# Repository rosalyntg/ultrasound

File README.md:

# Ultrasound

This repository contains the PCB design files, FPGA firmware files, and host software for a hobby 8 channel ultrasound system. It can do phased array operation. Here's an example of the pulse in my forearm:

Picture of the functioning ultrasound system:

## Overview

The parts of the ultrasound consist of:
- The probe, which is a Acuvision 4V1c probe bought off ebay
    - As far as I can tell, it has 112 elements. I think a bunch of them are broken for this unit, so I've atttempted to work around as best as possible
- The power board
    - This provides a variable voltage positive and negative rails for the pulser, -80V to +80V, as well as various low voltage supplies for the rest of the system (2.5V, 3.3V, +10V, -10V)
- The main logic board
    - Contains an AXAU15 FPGA SOM
      - 10G ethernet
      - JESD204b for the ADCs
      - Pulser logic
      - VGA control logic
      - Power supply control logic
    - 2x Ti ADC34J22 quad ADCs
        - And clock synthesis IC (Si5338)
    - 4x AD8332 dual LNA/VGA
    - 2x HV7321 quad ultrasound pulsers
    - Variable rate linear ramp circuit to control VGA gain
    - 10G ethernet interface
- Probe breakout board
    - Breaks out the connections from the probe to the main logic board, allowing for use of different probes without reworking the main board every time

The FPGA streams all the ADC data (~4Gbps) out the ethernet port to be processed on a host computer. The software programms beamforming patterns into the FPGA and interprets the ADC data

## Repo Tour

- `fpga/` - Contains the FPGA firmware that runs on the AXAU15 FPGA SOM
- `host/` - Contains the host software that communicates with the FPGA and processes the ADC data
- `pcb/ultrasound` - Contains the PCB design files for the main board
- `pcb/probe` - Contains the PCB design files for the probe breakout board
- `pcb/power-board` - Contains the PCB design files for the power board
- `pcb/simulations` - Contains various supporting spice simulations

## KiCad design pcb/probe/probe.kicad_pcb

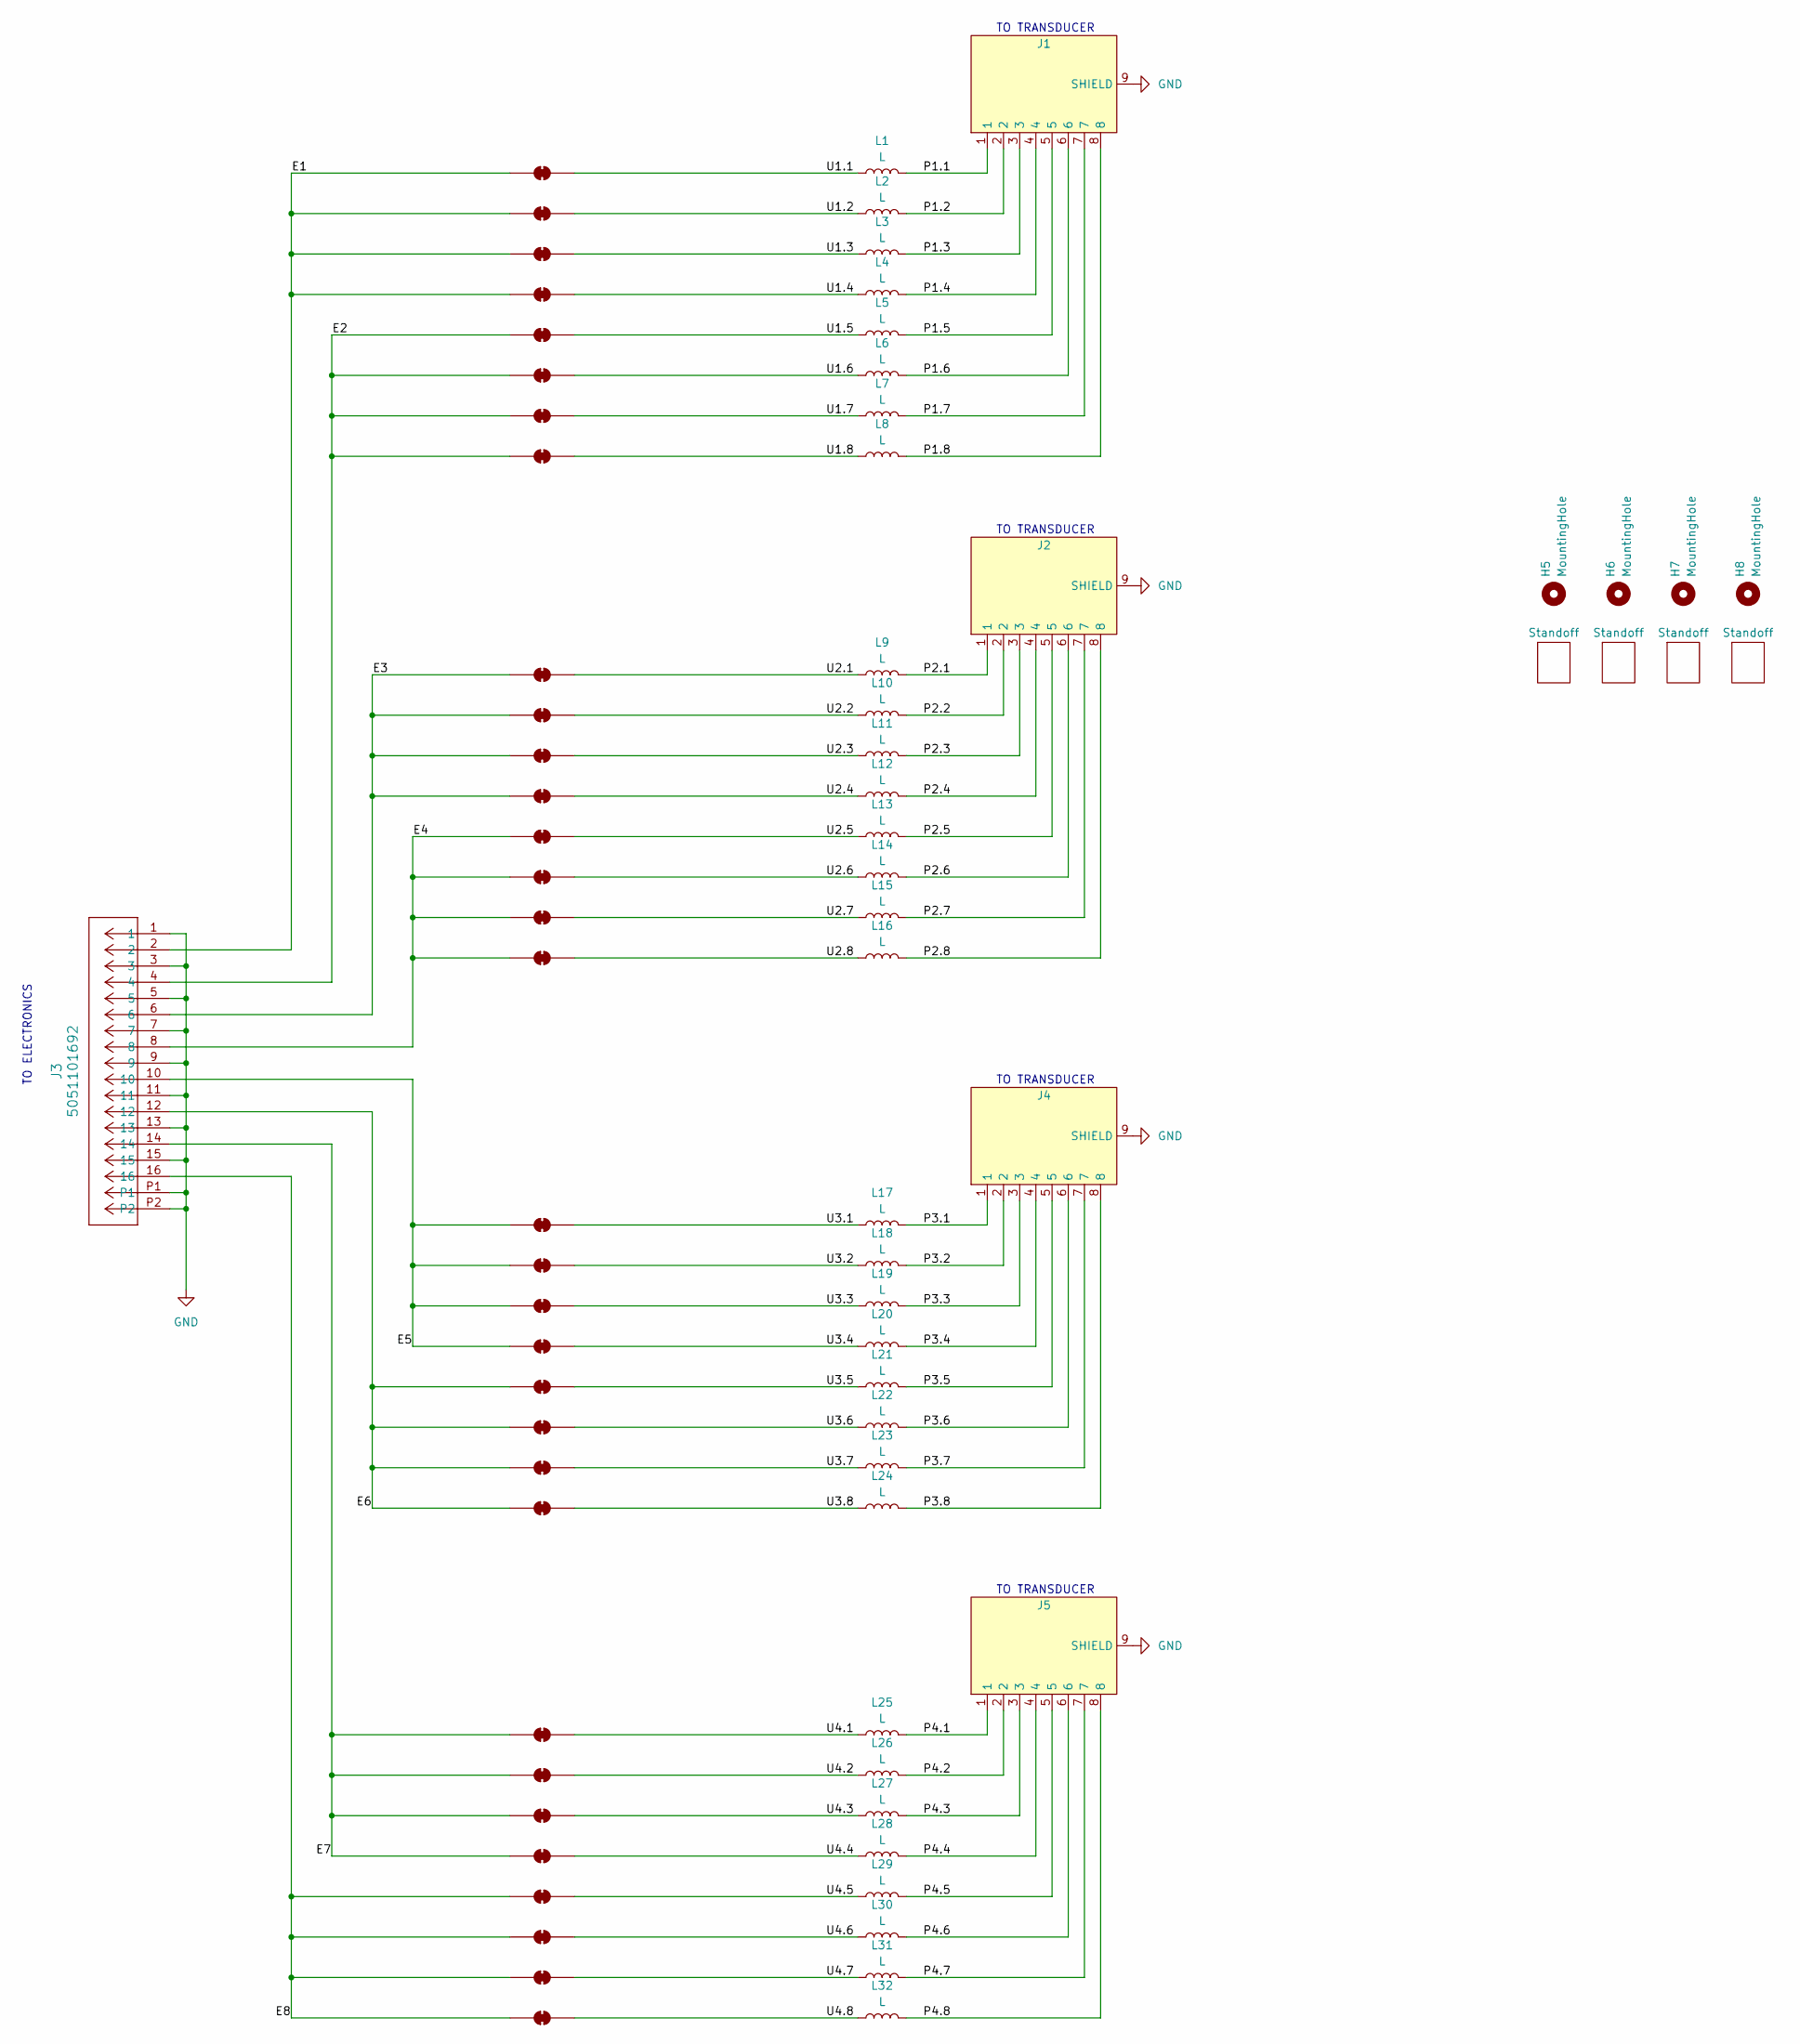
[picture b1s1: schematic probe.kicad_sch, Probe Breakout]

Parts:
H5, H6, H7, H8: MountingHole; MountingHole_3.2mm_M3
J1, J2, J4, J5: UCOAX
J3: 5051101692; CON_5051101692_MOL; Manufacturer Part Number 5051101692; Digikey Part Number WM12372CT-ND
JP2, JP3, JP4, JP5, JP6, JP7, JP8, JP9, JP10, JP11, JP12, JP13, JP14, JP15, JP16, JP17, JP18, JP19, JP20, JP21, JP22, JP23, JP24, JP25, JP26, JP27, JP28, JP29, JP30, JP31, JP32, JP33: SolderJumper_2_Bridged; SolderJumper-2_P1.3mm_Bridged_RoundedPad1.0x1.5mm
L1, L2, L3, L4, L5, L6, L7, L8, L9, L10, L11, L12, L13, L14, L15, L16, L17, L18, L19, L20, L21, L22, L23, L24, L25, L26, L27, L28, L29, L30, L31, L32: L; PROBE_INDUCTOR
Z8, Z9, Z10, Z11: Standoff; Manufacturer_Part_Number 24438; DigiKey Part Number 36-24438-ND

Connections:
/E1: J3.2, JP2.1 (A), JP3.1 (A), JP4.1 (A), JP5.1 (A)
/E2: J3.4, JP6.1 (A), JP7.1 (A), JP8.1 (A), JP9.1 (A)
/E3: J3.6, JP10.1 (A), JP11.1 (A), JP12.1 (A), JP13.1 (A)
/E4: J3.8, JP14.1 (A), JP15.1 (A), JP16.1 (A), JP17.1 (A)
/E5: J3.10, JP18.1 (A), JP19.1 (A), JP20.1 (A), JP21.1 (A)
/E6: J3.12, JP22.1 (A), JP23.1 (A), JP24.1 (A), JP25.1 (A)
/E7: J3.14, JP26.1 (A), JP27.1 (A), JP28.1 (A), JP29.1 (A)
/E8: J3.16, JP30.1 (A), JP31.1 (A), JP32.1 (A), JP33.1 (A)
/P1.1: J1.1, L1.2
/P1.2: J1.2, L2.2
/P1.3: J1.3, L3.2
/P1.4: J1.4, L4.2
/P1.5: J1.5, L5.2
/P1.6: J1.6, L6.2
/P1.7: J1.7, L7.2
/P1.8: J1.8, L8.2
/P2.1: J2.1, L9.2
/P2.2: J2.2, L10.2
/P2.3: J2.3, L11.2
/P2.4: J2.4, L12.2
/P2.5: J2.5, L13.2
/P2.6: J2.6, L14.2
/P2.7: J2.7, L15.2
/P2.8: J2.8, L16.2
/P3.1: J4.1, L17.2
/P3.2: J4.2, L18.2
/P3.3: J4.3, L19.2
/P3.4: J4.4, L20.2
/P3.5: J4.5, L21.2
/P3.6: J4.6, L22.2
/P3.7: J4.7, L23.2
/P3.8: J4.8, L24.2
/P4.1: J5.1, L25.2
/P4.2: J5.2, L26.2
/P4.3: J5.3, L27.2
/P4.4: J5.4, L28.2
/P4.5: J5.5, L29.2
/P4.6: J5.6, L30.2
/P4.7: J5.7, L31.2
/P4.8: J5.8, L32.2
/U1.1: JP2.2 (B), L1.1
/U1.2: JP3.2 (B), L2.1
/U1.3: JP4.2 (B), L3.1
/U1.4: JP5.2 (B), L4.1
/U1.5: JP6.2 (B), L5.1
/U1.6: JP7.2 (B), L6.1
/U1.7: JP8.2 (B), L7.1
/U1.8: JP9.2 (B), L8.1
/U2.1: JP10.2 (B), L9.1
/U2.2: JP11.2 (B), L10.1
/U2.3: JP12.2 (B), L11.1
/U2.4: JP13.2 (B), L12.1
/U2.5: JP14.2 (B), L13.1
/U2.6: JP15.2 (B), L14.1
/U2.7: JP16.2 (B), L15.1
/U2.8: JP17.2 (B), L16.1
/U3.1: JP18.2 (B), L17.1
/U3.2: JP19.2 (B), L18.1
/U3.3: JP20.2 (B), L19.1
/U3.4: JP21.2 (B), L20.1
/U3.5: JP22.2 (B), L21.1
/U3.6: JP23.2 (B), L22.1
/U3.7: JP24.2 (B), L23.1
/U3.8: JP25.2 (B), L24.1
/U4.1: JP26.2 (B), L25.1
/U4.2: JP27.2 (B), L26.1
/U4.3: JP28.2 (B), L27.1
/U4.4: JP29.2 (B), L28.1
/U4.5: JP30.2 (B), L29.1
/U4.6: JP31.2 (B), L30.1
/U4.7: JP32.2 (B), L31.1
/U4.8: JP33.2 (B), L32.1
GND: J1.9 (SHIELD), J2.9 (SHIELD), J3.1, J3.3, J3.5, J3.7, J3.9, J3.11, J3.13, J3.15, J3.P1, J3.P2, J4.9 (SHIELD), J5.9 (SHIELD)

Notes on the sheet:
TO ELECTRONICS
TO TRANSDUCER

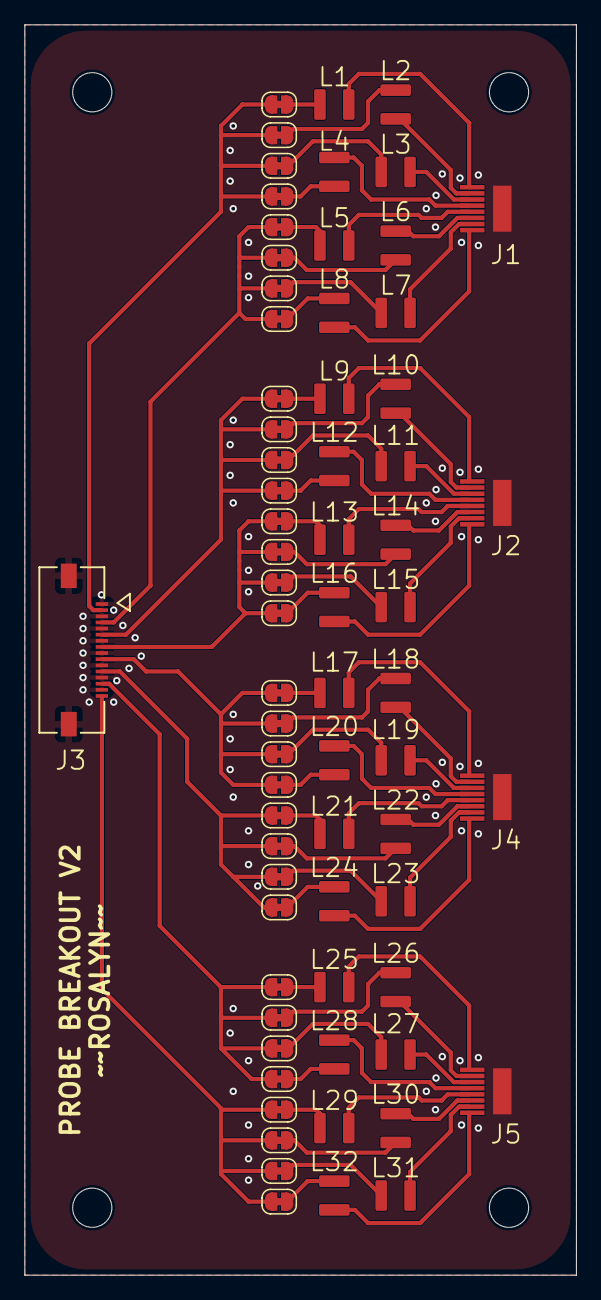
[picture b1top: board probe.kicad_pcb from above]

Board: 2 copper layers, 45.0 x 102.0 mm, 73 parts (0 on the bottom side), 73 nets.

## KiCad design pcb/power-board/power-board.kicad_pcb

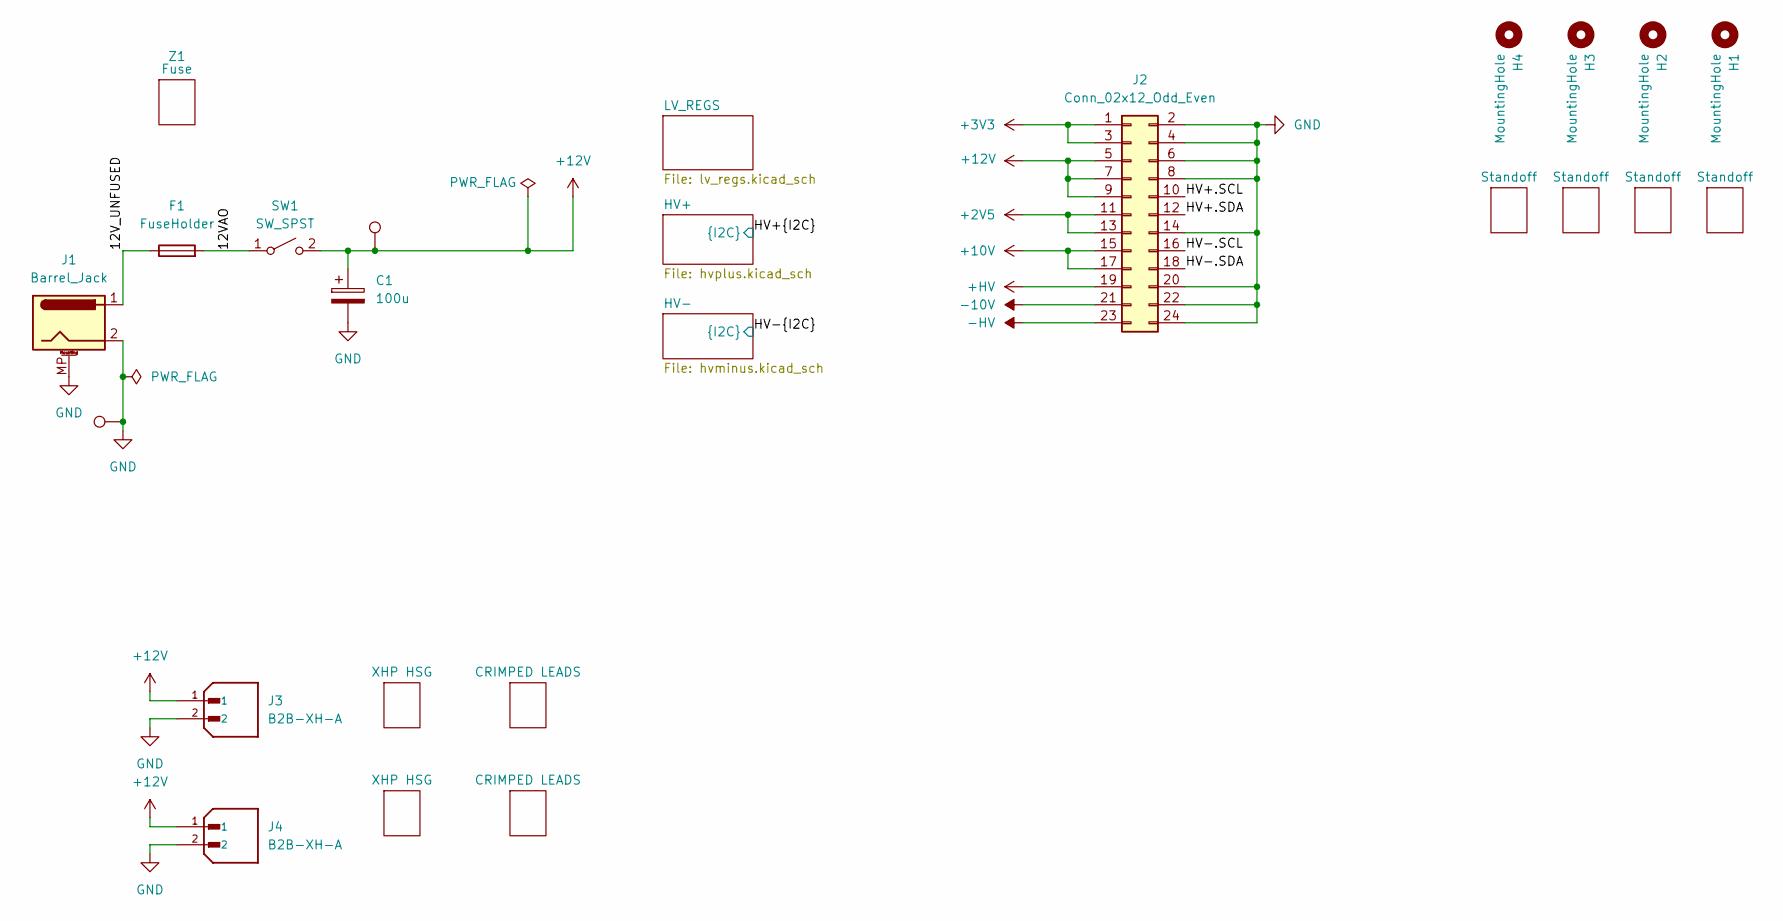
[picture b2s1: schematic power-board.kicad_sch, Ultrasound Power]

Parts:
C1: 100u; CP_Radial_D5.0mm_P2.00mm; Voltage Rating 16V; Manufacturer_Part_Number 860010372006; DigiKey Part Number 732-8598-3-ND
F1: FuseHolder; Fuseholder_Blade_Mini_Keystone_3568; Manufacturer_Part_Number 3568; DigiKey Part Number 36-3568-ND
H1, H2, H3, H4: MountingHole; MountingHole_3.2mm_M3
J1: Barrel_Jack; BarrelJack_CUI_PJ-063AH_Horizontal; Manufacturer_Part_Number PJ-063AH; DigiKey Part Number CP-063AH-ND
J2: Conn_02x12_Odd_Even; PinSocket_2x12_P2.54mm_Horizontal; Manufacturer_Part_Number PPPC122LJBN-RC; DigiKey Part Number S5565-ND
J3, J4: B2B-XH-A; JST_XH_B2B-XH-AM_1x02_P2.50mm_Vertical; Manufacturer_Part_Number B2B-XH-A; DigiKey Part Number 455-B2B-XH-A-ND
SW1: SW_SPST; CK_L101011; Manufacturer_Part_Number L101011MS02Q; DigiKey Part Number CKC5106-ND
TP1, TP2: TestPoint; TestPoint_THTPad_2.5x2.5mm_Drill1.2mm
Z1: Fuse; Manufacturer_Part_Number 0297005.WXNV; DigiKey Part Number F989-ND
Z8, Z9, Z10, Z11: Standoff; Manufacturer_Part_Number 24438; DigiKey Part Number 36-24438-ND
Z12, Z13: XHP HSG; Manufacturer_Part_Number XHP-2; DigiKey Part Number 455-2266-ND
Z14, Z15: CRIMPED LEADS; Manufacturer_Part_Number ASXHSXH22K305; DigiKey Part Number 455-3241-ND

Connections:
+2V5: J2.11, J2.13; also elsewhere on the board
+3V3: J2.1, J2.3; also elsewhere on the board
+10V: J2.15, J2.17; also elsewhere on the board
+12V: C1.1, J2.5, J2.7, J2.9, J3.1, J4.1, SW1.2 (B), TP2.1 (1_1); also elsewhere on the board
+HV: J2.19; also elsewhere on the board
-10V: J2.21; also elsewhere on the board
-HV: J2.23; also elsewhere on the board
/12VAO: F1.2, SW1.1 (A)
/12V_UNFUSED: F1.1, J1.1
/HV+.SCL: J2.10; also elsewhere on the board
/HV+.SDA: J2.12; also elsewhere on the board
/HV-.SCL: J2.16; also elsewhere on the board
/HV-.SDA: J2.18; also elsewhere on the board
GND: C1.2, J1.2, J1.MP (MountPin_MP), J2.2, J2.4, J2.6, J2.8, J2.14, J2.20, J2.22, J2.24, J3.2, J4.2, TP1.1 (1_1); also elsewhere on the board

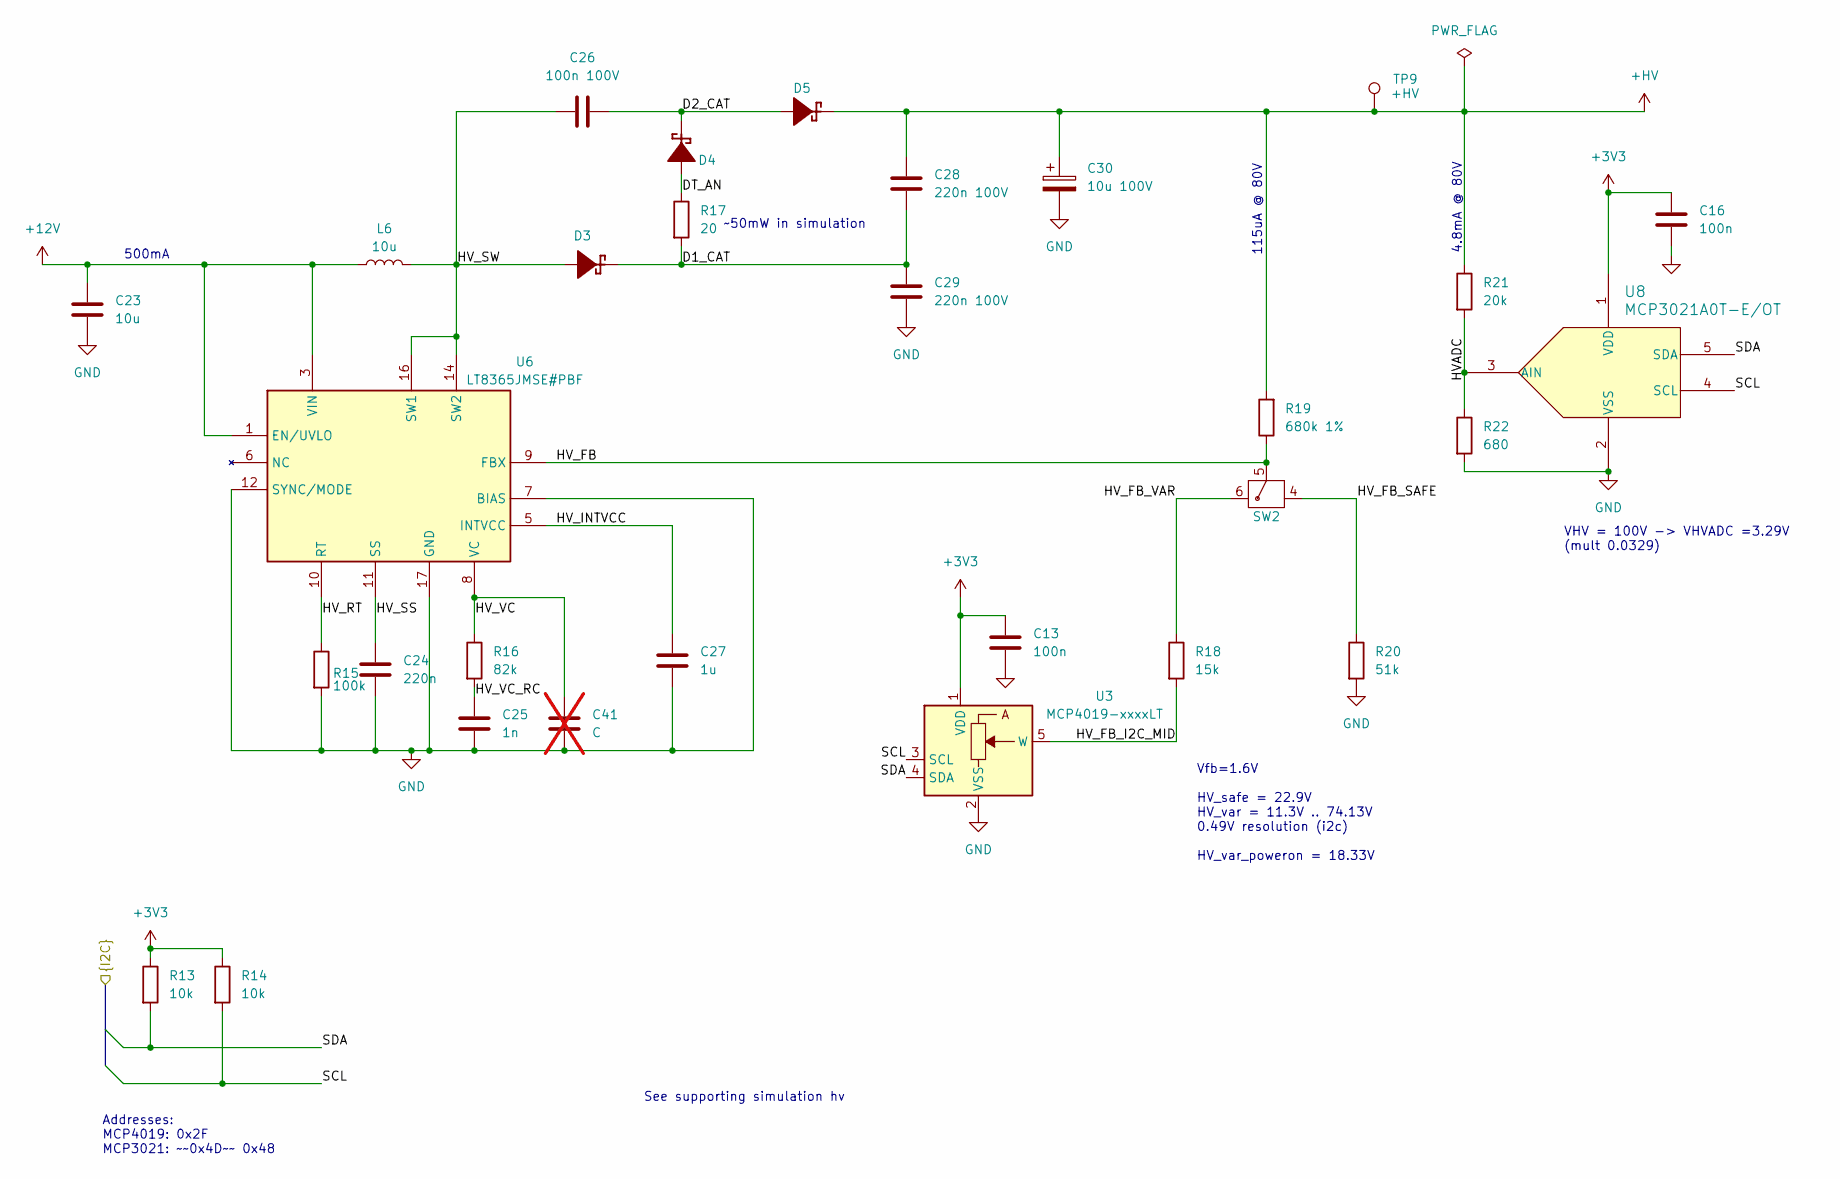
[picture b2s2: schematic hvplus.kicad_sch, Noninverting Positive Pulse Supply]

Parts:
C13, C16: 100n; C_0805_2012Metric_Pad1.18x1.45mm_HandSolder; Voltage Rating 25V; Manufacturer_Part_Number GCM21BR71E104KA37L; DigiKey Part Number 490-14779-1-ND
C23: 10u; C_0805_2012Metric_Pad1.18x1.45mm_HandSolder; Voltage Rating 25V; Manufacturer_Part_Number GRM21BR61E106KA73K; DigiKey Part Number 490-16824-2-ND
C24: 220n; C_0805_2012Metric_Pad1.18x1.45mm_HandSolder; Voltage Rating 25V; Manufacturer_Part_Number GRM219R71E224KA01D; DigiKey Part Number 490-1675-2-ND
C25: 1n; C_0805_2012Metric_Pad1.18x1.45mm_HandSolder; Voltage Rating 50V; Manufacturer_Part_Number GRM216R71H102KA01D
C26: 100n 100V; C_0805_2012Metric_Pad1.18x1.45mm_HandSolder; Voltage Rating 100V; Manufacturer_Part_Number GCM21BR72A104KA37L; DigiKey Part Number 490-4789-1-ND
C27: 1u; C_0805_2012Metric_Pad1.18x1.45mm_HandSolder; Voltage Rating 10V; Manufacturer_Part_Number GRM21BR71A105KA01L
C28, C29: 220n 100V; C_1210_3225Metric_Pad1.33x2.70mm_HandSolder; Voltage Rating 200V; Manufacturer_Part_Number GRM32DR72D224KW01L; DigiKey Part Number 490-13380-1-ND
C30: 10u 100V; CP_Radial_D10.0mm_P5.00mm; Voltage Rating 200V; Manufacturer_Part_Number ECA-2DHG100; DigiKey Part Number P19449-ND
C41: C; C_0805_2012Metric_Pad1.18x1.45mm_HandSolder; not fitted
D3, D4, D5: SMD1150PL-TP; SMD1150PL; Voltage Rating 150V; Mouser Part Number 621-DFLS1150-7
L6: 10u; WURTH_WE-LHMI-4.45mm; Mouser Part Number 710-74437324100
R13, R14: 10k; R_0805_2012Metric_Pad1.20x1.40mm_HandSolder; Manufacturer_Part_Number RC0805JR-0710K
R15: 100k; R_0805_2012Metric_Pad1.20x1.40mm_HandSolder; Manufacturer_Part_Number RC0805JR-07100R; DigiKey Part Number 311-107KCRCT-ND
R16: 82k; R_0805_2012Metric_Pad1.20x1.40mm_HandSolder; Manufacturer_Part_Number RC0805JR-0782K
R17: 20; R_0805_2012Metric_Pad1.20x1.40mm_HandSolder; Manufacturer_Part_Number RC0805JR-0720R
R18: 15k; R_0805_2012Metric_Pad1.20x1.40mm_HandSolder; Manufacturer_Part_Number RC0805FR-0712KL; DigiKey Part Number RC0805JR-0715K
R19: 680k 1%; R_0805_2012Metric_Pad1.20x1.40mm_HandSolder; Manufacturer_Part_Number RC0805FR-07680KL; DigiKey Part Number 311-680KCRCT-ND
R20: 51k; R_0805_2012Metric_Pad1.20x1.40mm_HandSolder; Manufacturer_Part_Number RC0805JR0751K; DigiKey Part Number 311-51KARCT-ND
R21: 20k; R_0805_2012Metric_Pad1.20x1.40mm_HandSolder; Manufacturer_Part_Number RC0805FR-071ML; DigiKey Part Number 311-1.00MCRCT-ND
R22: 680; R_0805_2012Metric_Pad1.20x1.40mm_HandSolder; Manufacturer_Part_Number AC0805FR-0727KL; DigiKey Part Number 13-AC0805FR-0727KLCT-ND
SW2: CST11T2CR; Manufacturer_Part_Number CST11T2CR; DigiKey Part Number 2449-CST11T2CR-ND
TP9: TestPoint; TestPoint_THTPad_2.5x2.5mm_Drill1.2mm
U3: MCP4019-xxxxLT; SOT-353_SC-70-5; Manufacturer_Part_Number MCP4018T-104E/LTY; DigiKey Part Number 150-MCP4018T-104E/LTYCT-ND
U6: LT8365JMSE#PBF; LT8365JMSEPBF; Mouser Part Number 584-LT8365JMSE#PBF
U8: MCP3021A0T-E/OT; SOT-23-5_MC_MCH-M; Manufacturer_Part_Number MCP3021A0T-E/OT; DigiKey Part Number MCP3021A0T-E/OTCT-ND

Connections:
+3V3: C13.1, C16.1, R13.1, R14.1, U3.1 (VDD), U8.1 (VDD); also elsewhere on the board
+12V: C23.1, L6.1, U6.1 (EN/UVLO), U6.3 (VIN); also elsewhere on the board
+HV: C28.1, C30.1, D5.1 (K), R19.2, R21.1, TP9.1 (1_1); also elsewhere on the board
/HV+.SCL: R14.2, U3.3 (SCL), U8.4 (SCL); also elsewhere on the board
/HV+.SDA: R13.2, U3.4 (SDA), U8.5 (SDA); also elsewhere on the board
/HV+/D1_CAT: C28.2, C29.1, D3.1 (K), R17.2
/HV+/D2_CAT: C26.2, D4.1 (K), D5.2 (A)
/HV+/DT_AN: D4.2 (A), R17.1
/HV+/HVADC: R21.2, R22.1, U8.3 (AIN)
/HV+/HV_FB: R19.1, SW2.5, U6.9 (FBX)
/HV+/HV_FB_I2C_MID: R18.2, U3.5 (W)
/HV+/HV_FB_SAFE: R20.1, SW2.4
/HV+/HV_FB_VAR: R18.1, SW2.6
/HV+/HV_INTVCC: C27.1, U6.5 (INTVCC)
/HV+/HV_RT: R15.1, U6.10 (RT)
/HV+/HV_SS: C24.1, U6.11 (SS)
/HV+/HV_SW: C26.1, D3.2 (A), L6.2, U6.14 (SW2), U6.16 (SW1)
/HV+/HV_VC: C41.1, R16.1, U6.8 (VC)
/HV+/HV_VC_RC: C25.1, R16.2
GND: C13.2, C16.2, C23.2, C24.2, C25.2, C27.2, C29.2, C30.2, C41.2, R15.2, R20.2, R22.2, U3.2 (VSS), U6.7 (BIAS), U6.12 (SYNC/MODE), U6.17 (GND), U8.2 (VSS); also elsewhere on the board

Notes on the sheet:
4.8mA @ 80V
~50mW in simulation
500mA
See supporting simulation hv
115uA @ 80V
Vfb=1.6V HV_safe = 22.9V HV_var = 11.3V .. 74.13V 0.49V resolution (i2c) HV_var_poweron = 18.33V
VHV = 100V -> VHVADC =3.29V (mult 0.0329)
Addresses: MCP4019: 0x2F MCP3021: ~~0x4D~~ 0x48

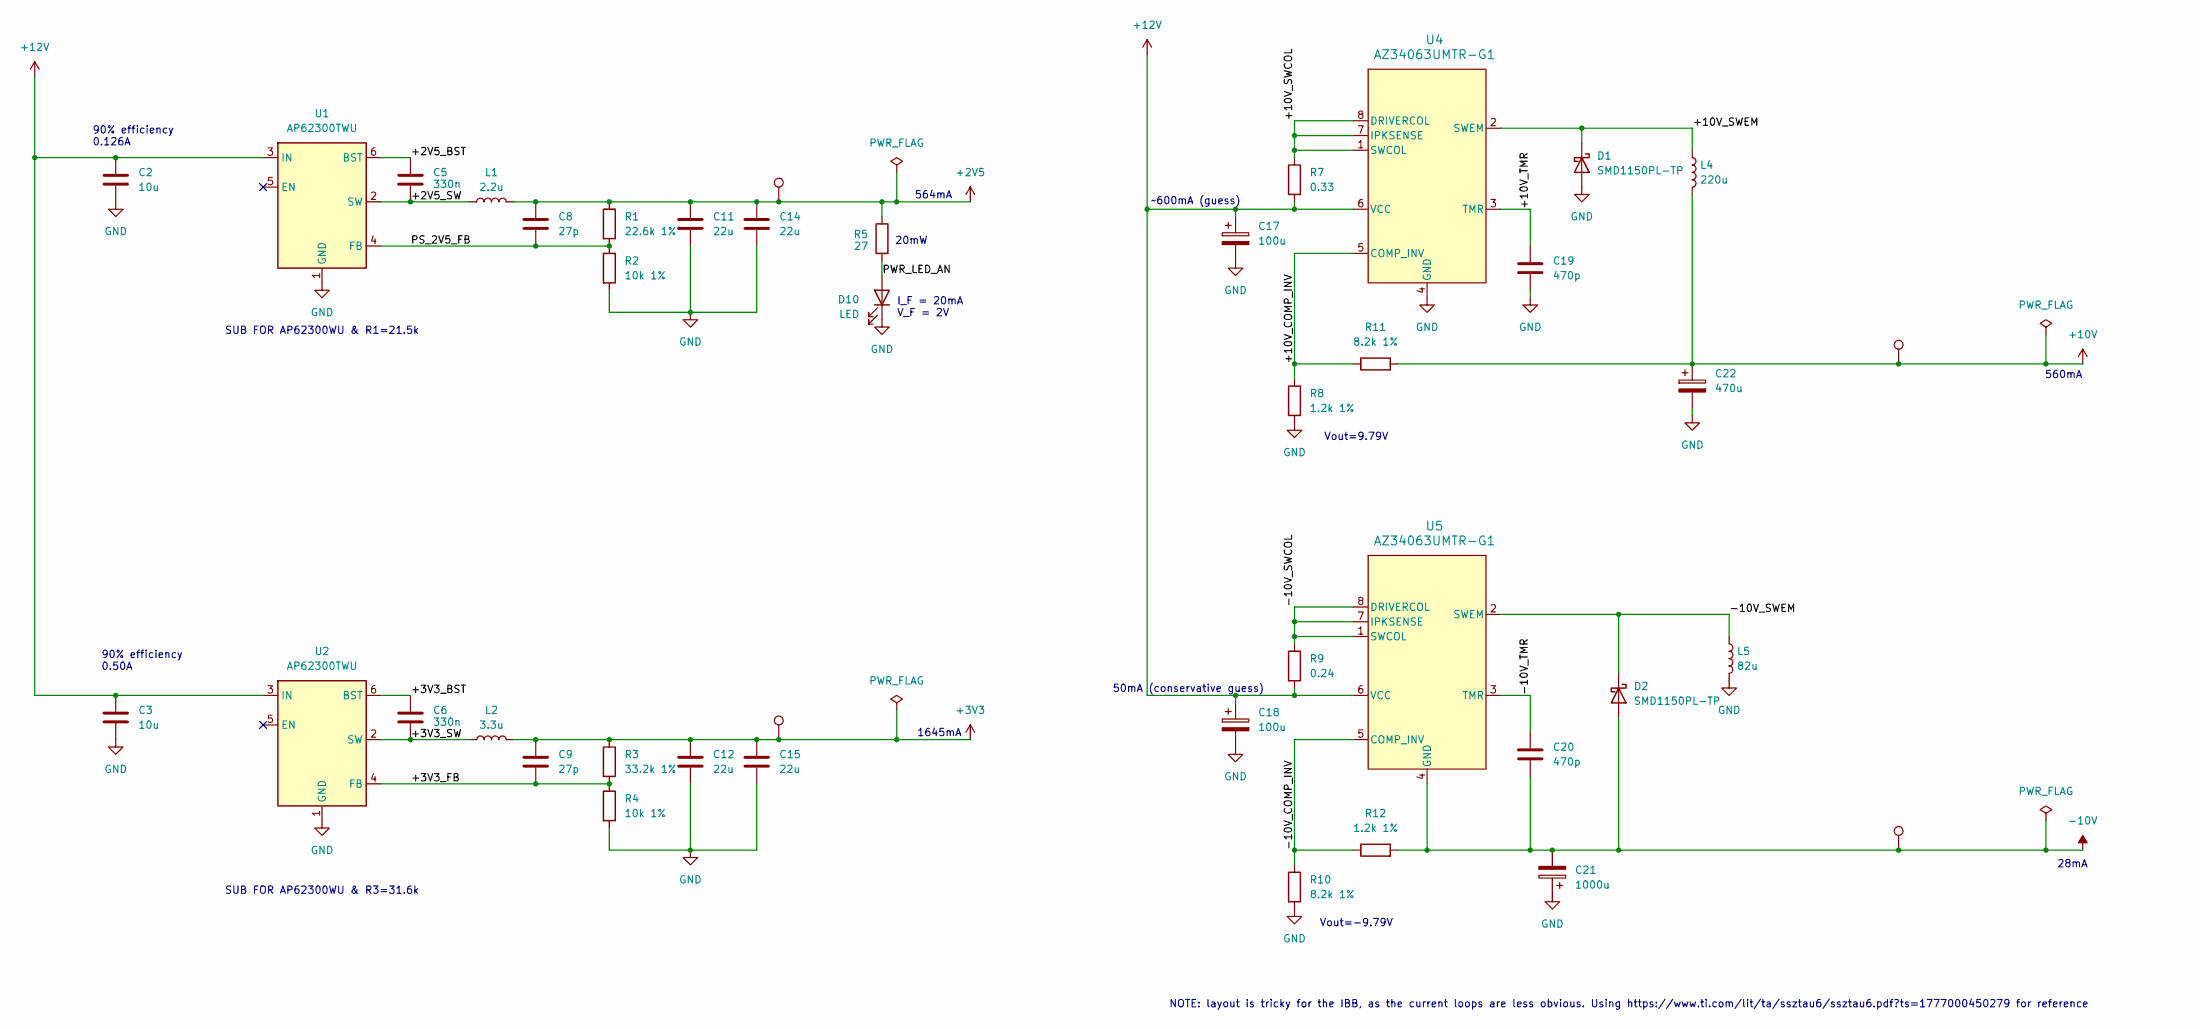
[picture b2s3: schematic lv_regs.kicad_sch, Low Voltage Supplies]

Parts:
C2, C3: 10u; C_0805_2012Metric_Pad1.18x1.45mm_HandSolder; Voltage Rating 25V; Manufacturer_Part_Number GRM21BR61E106KA73K; DigiKey Part Number 490-16824-2-ND
C5, C6: 330n; C_0805_2012Metric_Pad1.18x1.45mm_HandSolder; Voltage Rating 25V; Manufacturer_Part_Number GRM31C5C1E334JE01L; DigiKey Part Number 490-1677-2-ND
C8, C9: 27p; C_0805_2012Metric_Pad1.18x1.45mm_HandSolder; Voltage Rating 50V; Manufacturer_Part_Number GRM2165C1H270JZ01D
C11, C12, C14, C15: 22u; C_0805_2012Metric_Pad1.18x1.45mm_HandSolder; Voltage Rating 25V; Manufacturer_Part_Number GRM21BR71E334KA01L; DigiKey Part Number 490-10749-1-ND
C17, C18: 100u; CP_Radial_D5.0mm_P2.00mm; Voltage Rating 16V; Manufacturer_Part_Number 860010372006; DigiKey Part Number 732-8598-3-ND
C19, C20: 470p; C_0805_2012Metric_Pad1.18x1.45mm_HandSolder; Voltage Rating 50V; Manufacturer_Part_Number GRM2165C1H471JA01D; DigiKey Part Number 490-1617-2-ND
C21: 1000u; CP_Radial_D10.0mm_P5.00mm; Voltage Rating 16V; Manufacturer_Part_Number 860020375017; DigiKey Part Number 732-8804-3-ND
C22: 470u; CP_Radial_D8.0mm_P3.50mm; Voltage Rating 16V; Manufacturer_Part_Number 860020374012; DigiKey Part Number 732-8799-3-ND
D1, D2: SMD1150PL-TP; SMD1150PL; Voltage Rating 150V; Manufacturer_Part_Number SMD1150PL-TP; DigiKey Part Number SMD1150PL-TPMSCT-ND
D10: LED; LED_0805_2012Metric_Pad1.15x1.40mm_HandSolder; Manufacturer_Part_Number LTST-C171KRKT; DigiKey Part Number 160-1427-1-ND
L1: 2.2u; L_Murata_DFE201610P; Manufacturer_Part_Number DFE201610E-2R2M=P2; DigiKey Part Number 490-17728-1-ND
L2: 3.3u; L_1210_3225Metric_Pad1.42x2.65mm_HandSolder; Manufacturer_Part_Number IHLP1210BZEZ3R3M5A; DigiKey Part Number 541-IHLP1210BZEZ3R3M5ACT-ND
L4: 220u; L_Wuerth_WE-PDF_Handsoldering; Manufacturer_Part_Number 7447714221; DigiKey Part Number 732-4110-2-ND
L5: 82u; L_Wuerth_WE-PDF_Handsoldering; Manufacturer_Part_Number 7447714820; DigiKey Part Number 732-4109-2-ND
R1: 22.6k 1%; R_0805_2012Metric_Pad1.20x1.40mm_HandSolder; Manufacturer_Part_Number RC0805FR-0722K6L; DigiKey Part Number 311-22.6KCRCT-ND
R2, R4: 10k 1%; R_0805_2012Metric_Pad1.20x1.40mm_HandSolder; Manufacturer_Part_Number RC0805FR-0710KL; DigiKey Part Number 311-10.0KCRTR-ND
R3: 33.2k 1%; R_0805_2012Metric_Pad1.20x1.40mm_HandSolder; Manufacturer_Part_Number RC0805FR-0733K2L; DigiKey Part Number 311-33.2KCRTR-ND
R5: 27; R_0805_2012Metric_Pad1.20x1.40mm_HandSolder; Manufacturer_Part_Number RC0805JR-0727R
R7: 0.33; R_0805_2012Metric_Pad1.20x1.40mm_HandSolder; Manufacturer_Part_Number RL0805JR-070R33L; DigiKey Part Number 13-RL0805JR-070R33LCT-ND
R8, R12: 1.2k 1%; R_0805_2012Metric_Pad1.20x1.40mm_HandSolder; Manufacturer_Part_Number RC0805FR-131K2L; DigiKey Part Number 13-RC0805FR-131K2LCT-ND
R9: 0.24; R_0805_2012Metric_Pad1.20x1.40mm_HandSolder; Manufacturer_Part_Number RL0805FR-070R24L; DigiKey Part Number 311-.24SCT-ND
R10, R11: 8.2k 1%; R_0805_2012Metric_Pad1.20x1.40mm_HandSolder; Manufacturer_Part_Number RC0805FR-138K2L; DigiKey Part Number 13-RC0805FR-138K2LCT-ND
TP3, TP4, TP6, TP7: TestPoint; TestPoint_THTPad_2.5x2.5mm_Drill1.2mm
U1, U2: AP62300TWU; TSOT-23-6; Manufacturer_Part_Number AP62300TWU-7; DigiKey Part Number 31-AP62300TWU-7CT-ND
U4, U5: AZ34063UMTR-G1; SO-8_AZ3406-M_DIO-M; Manufacturer_Part_Number AZ34063UMTR-G1; DigiKey Part Number AZ34063UMTR-G1DICT-ND

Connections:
+2V5: C8.1, C11.1, C14.1, L1.2, R1.1, R5.1, TP3.1 (1_1); also elsewhere on the board
+3V3: C9.1, C12.1, C15.1, L2.2, R3.1, TP4.1 (1_1); also elsewhere on the board
+10V: C22.1, L4.2, R11.2, TP6.1 (1_1); also elsewhere on the board
+12V: C2.1, C3.1, C17.1, C18.1, R7.2, R9.2, U1.3 (IN), U2.3 (IN), U4.6 (VCC), U5.6 (VCC); also elsewhere on the board
-10V: C20.2, C21.2, D2.2 (A), R12.2, TP7.1 (1_1), U5.4 (GND); also elsewhere on the board
/LV_REGS/+2V5_BST: C5.1, U1.6 (BST)
/LV_REGS/+2V5_SW: C5.2, L1.1, U1.2 (SW)
/LV_REGS/+3V3_BST: C6.1, U2.6 (BST)
/LV_REGS/+3V3_FB: C9.2, R3.2, R4.1, U2.4 (FB)
/LV_REGS/+3V3_SW: C6.2, L2.1, U2.2 (SW)
/LV_REGS/+10V_COMP_INV: R8.1, R11.1, U4.5 (COMP_INV)
/LV_REGS/+10V_SWCOL: R7.1, U4.1 (SWCOL), U4.7 (IPKSENSE), U4.8 (DRIVERCOL)
/LV_REGS/+10V_SWEM: D1.1 (K), L4.1, U4.2 (SWEM)
/LV_REGS/+10V_TMR: C19.1, U4.3 (TMR)
/LV_REGS/-10V_COMP_INV: R10.1, R12.1, U5.5 (COMP_INV)
/LV_REGS/-10V_SWCOL: R9.1, U5.1 (SWCOL), U5.7 (IPKSENSE), U5.8 (DRIVERCOL)
/LV_REGS/-10V_SWEM: D2.1 (K), L5.1, U5.2 (SWEM)
/LV_REGS/-10V_TMR: C20.1, U5.3 (TMR)
/LV_REGS/PS_2V5_FB: C8.2, R1.2, R2.1, U1.4 (FB)
/LV_REGS/PWR_LED_AN: D10.2 (A), R5.2
GND: C2.2, C3.2, C11.2, C12.2, C14.2, C15.2, C17.2, C18.2, C19.2, C21.1, C22.2, D1.2 (A), D10.1 (K), L5.2, R2.2, R4.2, R8.2, R10.2, U1.1 (GND), U2.1 (GND), U4.4 (GND); also elsewhere on the board

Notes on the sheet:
20mW
I_F = 20mA V_F = 2V
564mA
1645mA
560mA
SUB FOR AP62300WU & R3=31.6k
Vout=-9.79V
Vout=9.79V
90% efficiency 0.126A
50mA (conservative guess)
28mA
90% efficiency 0.50A
~600mA (guess)
SUB FOR AP62300WU & R1=21.5k
NOTE: layout is tricky for the IBB, as the current loops are less obvious. Using https://www.ti.com/lit/ta/ssztau6/ssztau6.pdf?ts=1777000450279 for reference

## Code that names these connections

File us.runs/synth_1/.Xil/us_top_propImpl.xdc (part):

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set_property src_info {type:XDC file:1 line:47 export:INPUT save:INPUT read:READ} [current_design]
set_property PACKAGE_PIN AB15 [get_ports sfp_sda]
set_property src_info {type:XDC file:1 line:50 export:INPUT save:INPUT read:READ} [current_design]
set_property PACKAGE_PIN AA15 [get_ports pulser_oen]
set_property src_info {type:XDC file:1 line:52 export:INPUT save:INPUT read:READ} [current_design]
set_property PACKAGE_PIN Y15 [get_ports {pulser0_neg[1]}]
set_property src_info {type:XDC file:1 line:53 export:INPUT save:INPUT read:READ} [current_design]
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set_property src_info {type:XDC file:1 line:57 export:INPUT save:INPUT read:READ} [current_design]
set_property PACKAGE_PIN W15 [get_ports {pulser0_pos[1]}]
set_property src_info {type:XDC file:1 line:58 export:INPUT save:INPUT read:READ} [current_design]
set_property PACKAGE_PIN W14 [get_ports pulser_clk]
set_property src_info {type:XDC file:1 line:60 export:INPUT save:INPUT read:READ} [current_design]
set_property PACKAGE_PIN AA13 [get_ports {pulser1_neg[2]}]
set_property src_info {type:XDC file:1 line:61 export:INPUT save:INPUT read:READ} [current_design]
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set_property src_info {type:XDC file:1 line:64 export:INPUT save:INPUT read:READ} [current_design]
set_property PACKAGE_PIN AC13 [get_ports {pulser1_pos[3]}]
set_property src_info {type:XDC file:1 line:65 export:INPUT save:INPUT read:READ} [current_design]
set_property PACKAGE_PIN F13 [get_ports uart_rx]
set_property src_info {type:XDC file:1 line:66 export:INPUT save:INPUT read:READ} [current_design]
set_property PACKAGE_PIN F14 [get_ports uart_tx]
set_property src_info {type:XDC file:1 line:69 export:INPUT save:INPUT read:READ} [current_design]
set_property PACKAGE_PIN AC19 [get_ports jesd_coreclkp]
set_property src_info {type:XDC file:1 line:70 export:INPUT save:INPUT read:READ} [current_design]
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set_property src_info {type:XDC file:1 line:90 export:INPUT save:INPUT read:READ} [current_design]
set_property PACKAGE_PIN P25 [get_ports adc1_cs]
set_property src_info {type:XDC file:1 line:91 export:INPUT save:INPUT read:READ} [current_design]
set_property PACKAGE_PIN AB6 [get_ports eth_refclkn]
set_property src_info {type:XDC file:1 line:92 export:INPUT save:INPUT read:READ} [current_design]
set_property PACKAGE_PIN AB7 [get_ports eth_refclkp]
set_property src_info {type:XDC file:1 line:93 export:INPUT save:INPUT read:READ} [current_design]
set_property PACKAGE_PIN V7 [get_ports jesd_refclkp]
set_property src_info {type:XDC file:1 line:94 export:INPUT save:INPUT read:READ} [current_design]
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set_property src_info {type:XDC file:1 line:127 export:INPUT save:INPUT read:READ} [current_design]
set_property PACKAGE_PIN D9 [get_ports mux_le]
set_property src_info {type:XDC file:1 line:128 export:INPUT save:INPUT read:READ} [current_design]
set_property PACKAGE_PIN A10 [get_ports ramp_rst]
set_property src_info {type:XDC file:1 line:130 export:INPUT save:INPUT read:READ} [current_design]
set_property PACKAGE_PIN B10 [get_ports mux_clk]
set_property src_info {type:XDC file:1 line:132 export:INPUT save:INPUT read:READ} [current_design]
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set_property src_info {type:XDC file:1 line:137 export:INPUT save:INPUT read:READ} [current_design]
set_property PACKAGE_PIN AF14 [get_ports {test[5]}]
set_property src_info {type:XDC file:1 line:140 export:INPUT save:INPUT read:READ} [current_design]
set_property PACKAGE_PIN AD13 [get_ports sfp_mod_abs]
set_property src_info {type:XDC file:1 line:142 export:INPUT save:INPUT read:READ} [current_design]
set_property PACKAGE_PIN W20 [get_ports {test[0]}]
set_property src_info {type:XDC file:1 line:144 export:INPUT save:INPUT read:READ} [current_design]
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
